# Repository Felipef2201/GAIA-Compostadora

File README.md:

# GAIA-Compostadora
GAIA (Generador Autónomo Inteligente de Abono) / Compostadora semiautomática

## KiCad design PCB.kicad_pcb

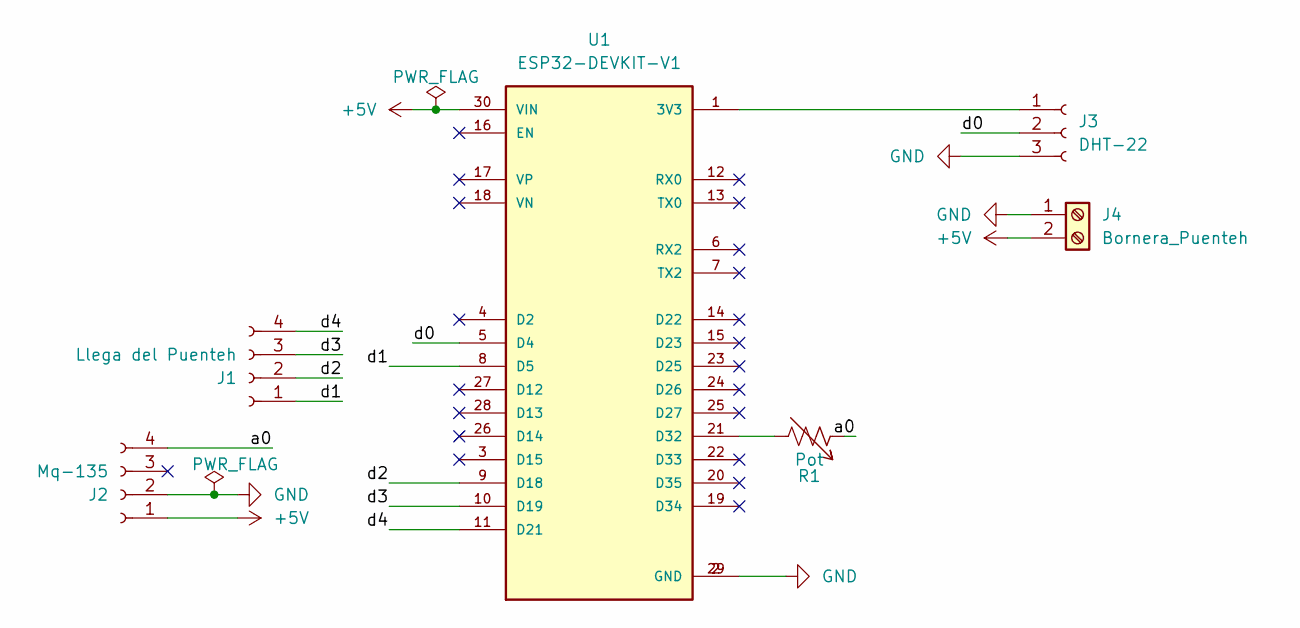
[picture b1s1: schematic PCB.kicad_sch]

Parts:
J1: Llega del Puenteh; PinSocket_1x04_P2.54mm_Vertical
J2: Mq-135; PinSocket_1x04_P2.54mm_Vertical
J3: DHT-22; PinSocket_1x03_P2.54mm_Vertical
J4: Bornera_Puenteh; TerminalBlock_bornier-2_P5.08mm
R1: Pot; Potentiometer_Bourns_3296W_Vertical
U1: ESP32-DEVKIT-V1; MODULE_ESP32_DEVKIT_V1; PARTREV N/A

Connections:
+5V: J2.1, J4.2, U1.30 (VIN)
/a0: J2.4, R1.1
/d0: J3.2, U1.5 (D4)
/d1: J1.1, U1.8 (D5)
/d2: J1.2, U1.9 (D18)
/d3: J1.3, U1.10 (D19)
/d4: J1.4, U1.11 (D21)
GND: J2.2, J3.3, J4.1, U1.2 (GND), U1.29 (GND)
unnamed: J3.1, U1.1 (3V3)
unnamed: R1.2, U1.21 (D32)

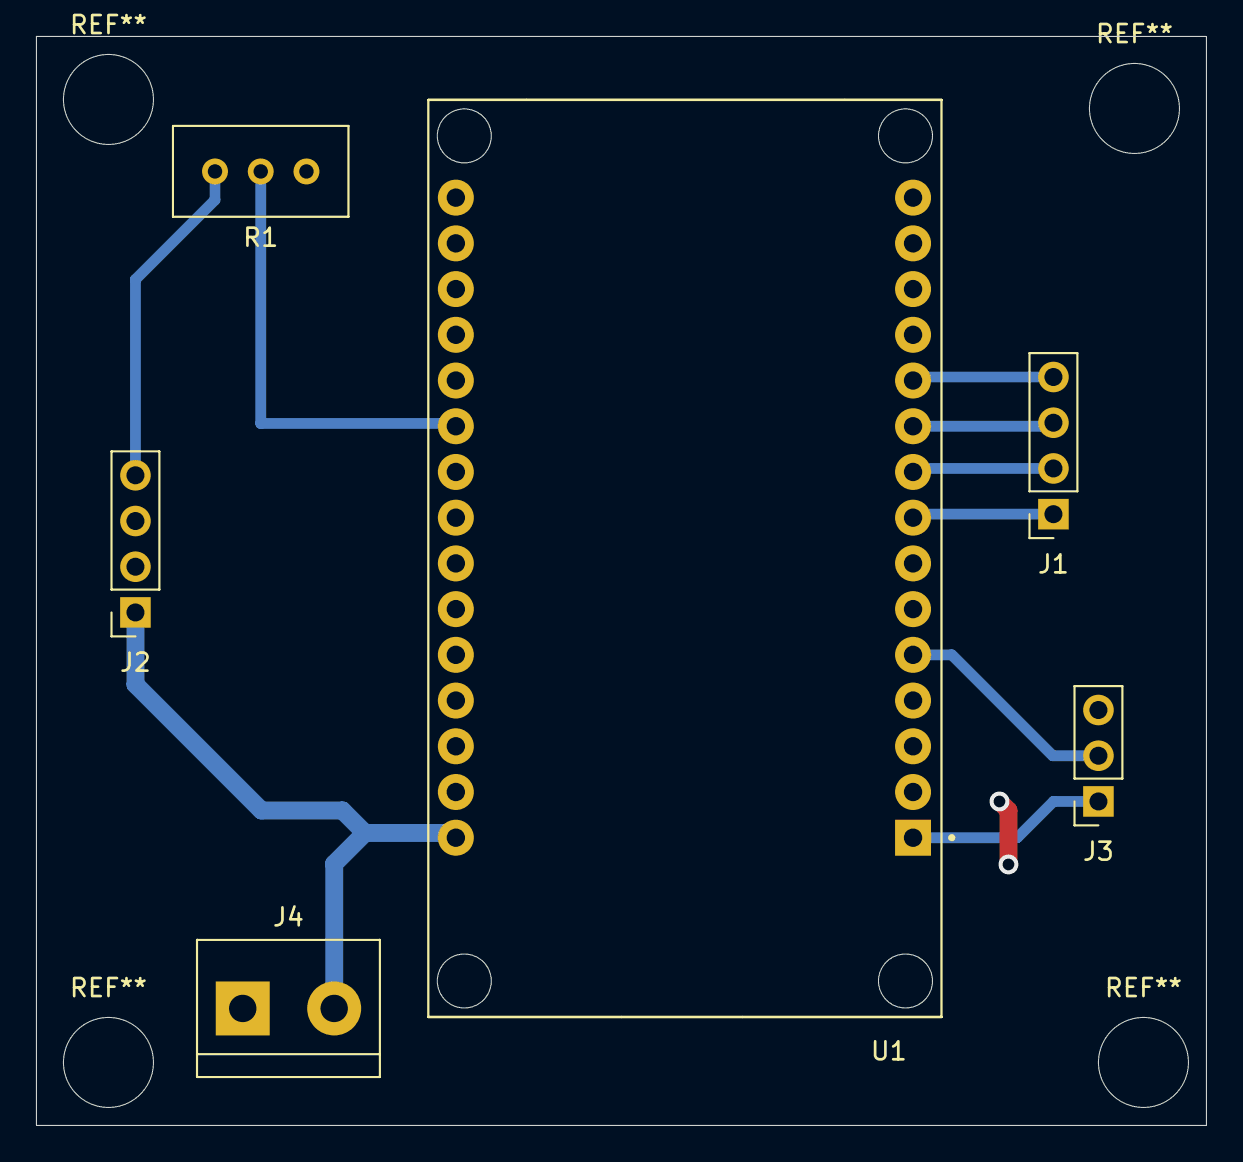
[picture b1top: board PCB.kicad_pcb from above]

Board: 2 copper layers, 65.0 x 60.5 mm, 6 parts (0 on the bottom side), 10 nets.

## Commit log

2025-07-19 Create PCB
2025-07-23 Archivos PCB
2025-07-23 Partes del diseño GAIA
2025-07-23 Update README.md
    Actualizacion nombre
